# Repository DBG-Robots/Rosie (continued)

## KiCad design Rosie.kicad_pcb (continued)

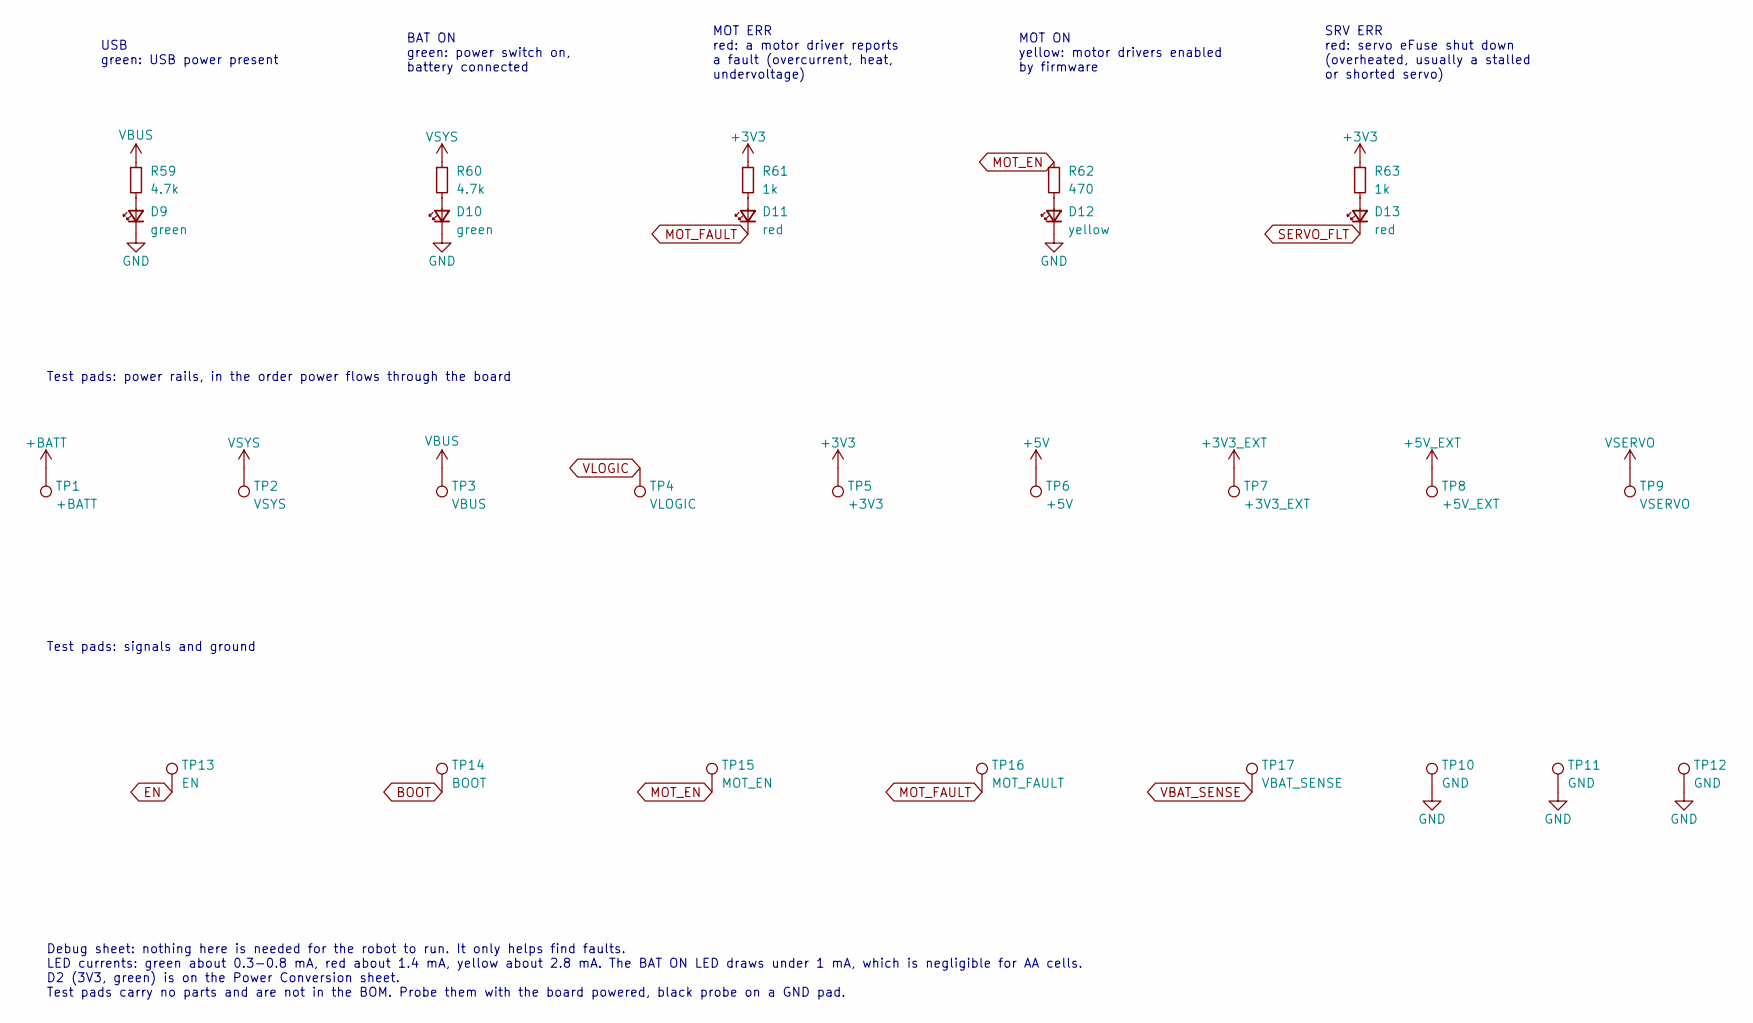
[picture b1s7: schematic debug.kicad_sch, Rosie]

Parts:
D9, D10: green; LED_0805_2012Metric; LCSC Part C2297
D11, D13: red; LED_0603_1608Metric; LCSC Part C2286
D12: yellow; LED_0805_2012Metric; LCSC Part C2296
R59, R60: 4.7k; R_0402_1005Metric
R61, R63: 1k; R_0402_1005Metric
R62: 470; R_0402_1005Metric
TP1: +BATT; TestPoint_Pad_D1.5mm
TP2: VSYS; TestPoint_Pad_D1.5mm
TP3: VBUS; TestPoint_Pad_D1.5mm
TP4: VLOGIC; TestPoint_Pad_D1.5mm
TP5: +3V3; TestPoint_Pad_D1.5mm
TP6: +5V; TestPoint_Pad_D1.5mm
TP7: +3V3_EXT; TestPoint_Pad_D1.5mm
TP8: +5V_EXT; TestPoint_Pad_D1.5mm
TP9: VSERVO; TestPoint_Pad_D1.5mm
TP10, TP11, TP12: GND; TestPoint_Pad_D1.5mm
TP13: EN; TestPoint_Pad_D1.5mm
TP14: BOOT; TestPoint_Pad_D1.5mm
TP15: MOT_EN; TestPoint_Pad_D1.5mm
TP16: MOT_FAULT; TestPoint_Pad_D1.5mm
TP17: VBAT_SENSE; TestPoint_Pad_D1.5mm

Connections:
+3V3: R61.1, R63.1, TP5.1; also elsewhere on the board
+3V3_EXT: TP7.1; also elsewhere on the board
+5V: TP6.1; also elsewhere on the board
+5V_EXT: TP8.1; also elsewhere on the board
+BATT: TP1.1; also elsewhere on the board
BOOT: TP14.1; also elsewhere on the board
EN: TP13.1; also elsewhere on the board
GND: D9.1 (K), D10.1 (K), D12.1 (K), TP10.1, TP11.1, TP12.1; also elsewhere on the board
MOT_EN: R62.1, TP15.1; also elsewhere on the board
MOT_FAULT: D11.1 (K), TP16.1; also elsewhere on the board
unnamed: D9.2 (A), R59.2
unnamed: D10.2 (A), R60.2
unnamed: D11.2 (A), R61.2
unnamed: D12.2 (A), R62.2
unnamed: D13.2 (A), R63.2
SERVO_FLT: D13.1 (K); also elsewhere on the board
VBAT_SENSE: TP17.1; also elsewhere on the board
VBUS: R59.1, TP3.1; also elsewhere on the board
VLOGIC: TP4.1; also elsewhere on the board
VSERVO: TP9.1; also elsewhere on the board
VSYS: R60.1, TP2.1; also elsewhere on the board

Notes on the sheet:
USB green: USB power present
BAT ON green: power switch on, battery connected
MOT ERR red: a motor driver reports a fault (overcurrent, heat, undervoltage)
MOT ON yellow: motor drivers enabled by firmware
SRV ERR red: servo eFuse shut down (overheated, usually a stalled or shorted servo)
Test pads: power rails, in the order power flows through the board
Test pads: signals and ground
Debug sheet: nothing here is needed for the robot to run. It only helps find faults. LED currents: green about 0.3-0.8 mA, red about 1.4 mA, yellow about 2.8 mA. The BAT ON LED draws under 1 mA, which is negligible for AA cells. D2 (3V3, green) is on the Power Conversion sheet. Test pads carry no p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

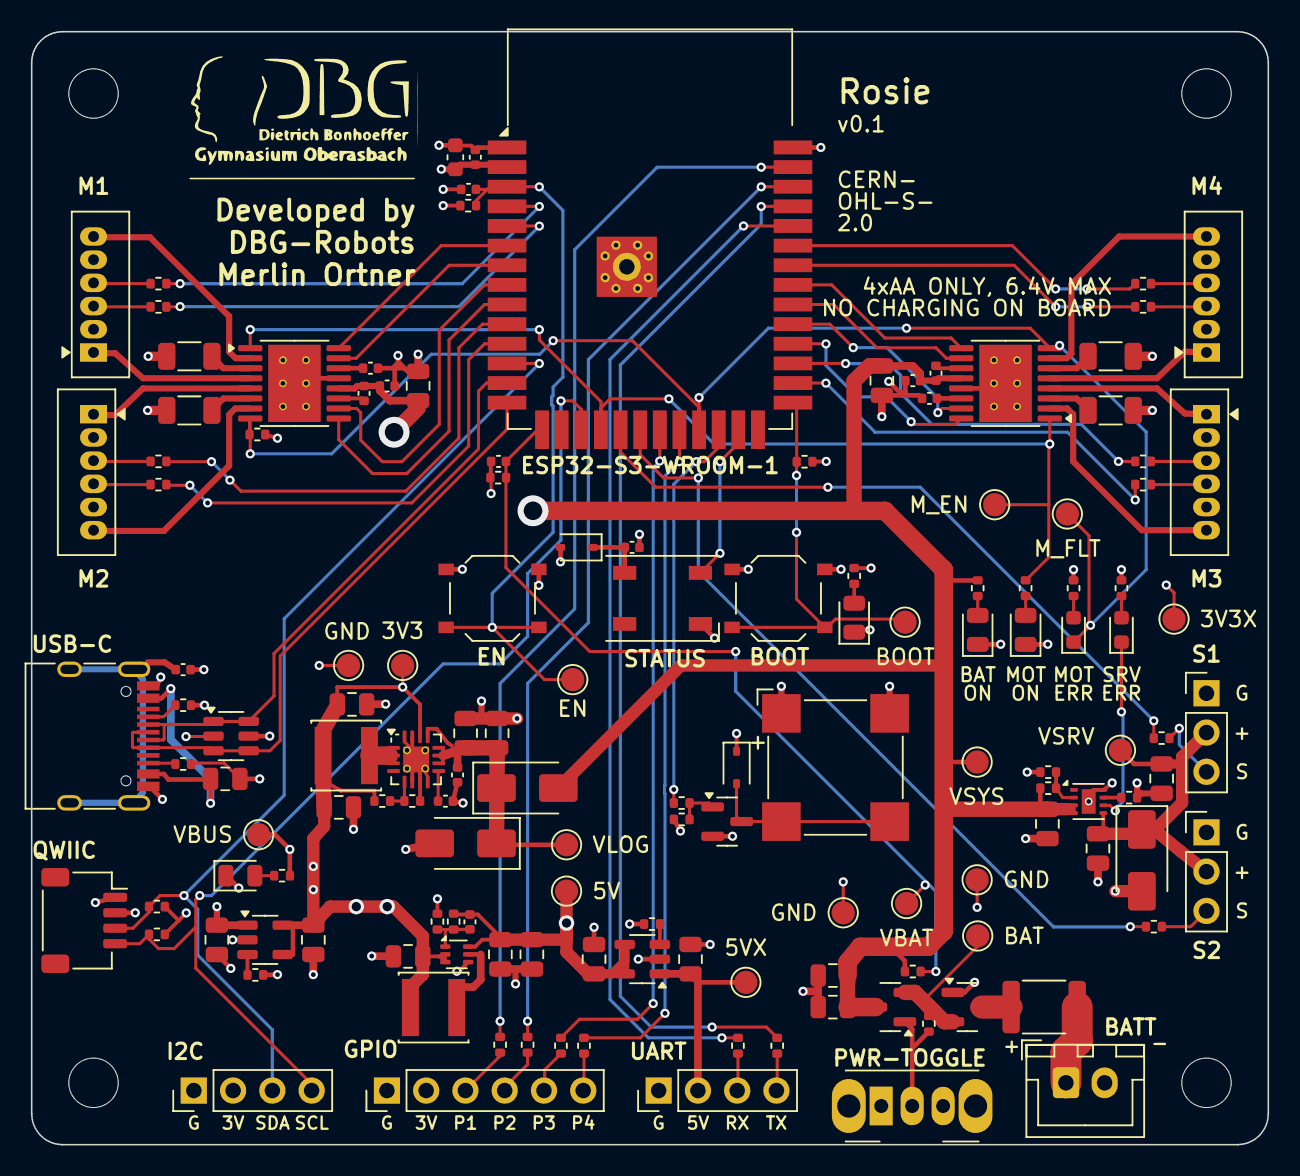
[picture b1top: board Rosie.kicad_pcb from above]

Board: 4 copper layers, 80.0 x 72.0 mm, 145 parts (0 on the bottom side), 102 nets.

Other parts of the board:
H1, H2, H3, H4: MountingHole_3.2mm_M3

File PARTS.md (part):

# Rosie – picked parts

JLCPCB **Economic PCBA only**. Basic/Preferred parts are free; each unique Extended part costs $3.07 per order.
Every pick below was checked as Economic-eligible and in stock on 2026-11-03 (power parts for the 4×AA design: 2026-11-04).

**Battery:** 4×AA in a flat holder under the board (NiMH 1900–2500 mAh, about 3 h; alkaline works too), 4.0–6.4 V.
The board never charges the cells: charge them in an external AA charger.
Resistors and capacitors aren't listed: JLC matches them by value and package. R43–R58 are 1 kΩ series resistors protecting every encoder, servo, UART and GPIO signal, so the pins on J12 can only source or sink about 1–2 mA. R59–R63 are the debug LED resistors (see below). Pick C47 (10 µF on VBUS) rated at least 16 V, because plugging in a USB cable can briefly overshoot 5 V.

## Assembled by JLC

| Function | Part | LCSC | Symbol | Footprint |
|---|---|---|---|---|
| Motor driver ×2 | DRV8833PWPR | C50506 | `Driver_Motor:DRV8833PWP` | `Package_SO:HTSSOP-16-1EP_4.4x5mm_P0.65mm_EP3.4x5mm_Mask2.46x2.31mm_ThermalVias` |
| 3.3 V buck (3–17 V in, 3 A, 100 % duty) | TPS62130ARGTR | C337502 | `Regulator_Switching:TPS62130A` | `Package_DFN_QFN:VQFN-16-1EP_3x3mm_P0.5mm_EP1.68x1.68mm_ThermalVias` |
| Servo eFuse (2 A, no OV clamp, auto-retry) | TPS259571DSGR | C471038 | `jlc:TPS259571DSG` | `Package_SON:WSON-8-1EP_2x2mm_P0.5mm_EP0.9x1.6mm` |
| Schottky ×3 (D6, D7: logic supply OR, battery / USB; D8: servo output clamp) | SS34 | C8678 (Basic) | `Diode:SS34` | `Diode_SMD:D_SMA` |
| Resettable fuse (3 A hold / 5 A trip, 8 V) | ASMD1812-300 | C135366 | `Device:Polyfuse` | `Fuse:Fuse_1812_4532Metric` |
| 5 V boost (from 3.3 V) | TPS61023DRLR | C919459 | `jlc:TPS61023DRL` | `Package_TO_SOT_SMD:SOT-563` |
| Current-limited switch ×2 (ext. 5 V / ext. 3.3 V) | SY6280AAC | C55136 | `jlc:SY6280AAC` | `Package_TO_SOT_SMD:SOT-23-5` |
| 1 µH inductor ×2 (18 mΩ, 4.7 A / 5.7 A) | FNR4030S1R0MT | C167865 | `Device:L` | `Inductor_SMD:L_Changjiang_FNR4030S` |
| P-FET ×2 (battery reverse polarity, power switch) | AO3401A | C15127 (Basic) | `Transistor_FET:AO3401A` | `Package_TO_SOT_SMD:SOT-23` |
| Qwiic I2C socket (J7) | JST SM04B-SRSS-TB(LF)(SN) | C160404 | `Connector_Generic:Conn_01x04` | `Connector_JST:JST_SH_SM04B-SRSS-TB_1x04-1MP_P1.00mm_Horizontal` |
| USB ESD | USBLC6-2SC6 | C7519 | `Power_Protection:USBLC6-2SC6` | `Package_TO_SOT_SMD:SOT-23-6` |
| USB-C receptacle | HRO TYPE-C-31-M-12 | C165948 | `Connector:USB_C_Receptacle_USB2.0_16P` | `Connector_USB:USB_C_Receptacle_HRO_TYPE-C-31-M-12` |
| RGB LED (WS2812B-compatible, 1 VDD / 2 DO / 3 GND / 4 DI) | XL-5050RGBC-2812B-HM | C48586674 | `LED:WS2812B` | `LED_SMD:LED_WS2812B_PLCC4_5.0x5.0mm_P3.2mm` |
| Buzzer (magnetic, 16 Ω) | MLT-8530 | C94599 | `Device:Buzzer` | `jlc:Buzzer_Huaneng_MLT-8530` |
| Buzzer driver NPN | MMBT3904 | C20526 (Basic) | `Transistor_BJT:MMBT3904` | `Package_TO_SOT_SMD:SOT-23` |
| Diode (buzzer flyback, RGB LED supply drop) | 1N4148WS | C2128 (Basic) | `Diode:1N4148WS` | `Diode_SMD:D_SOD-323` |
| Power LEDs, green (D2 3V3, D9 USB, D10 BAT ON) | KT-0805G | C2297 (Basic) | `Device:LED_Small` | `LED_SMD:LED_0805_2012Metric` |
| Motors-enabled LED, yellow (D12 MOT ON) | KT-0805Y | C2296 (Basic) | `Device:LED_Small` | `LED_SMD:LED_0805_2012Metric` |
| Fault LEDs, red (D11 MOT ERR, D13 SRV ERR) | KT-0603R | C2286 (Basic) | `Device:LED_Small` | `LED_SMD:LED_0603_1608Metric` |
| EN / BOOT buttons | TS-1187A-B-A-B | C318884 (Basic) | `Switch:SW_Push` | `Button_Switch_SMD:SW_Push_1P1T_XKB_TS-1187A` |

## Hand-soldered (order from LCSC, not placed by JLC)

| Function | Part | LCSC | Symbol | Footprint |
|---|---|---|---|---|
| MCU module | ESP32-S3-WROOM-1-N8R2 | C2913204 | `RF_Module:ESP32-S3-WROOM-1` | `jlc:ESP32-S3-WROOM-1_HandSolder` (longer pads, no paste, solder hole in the ground pad) |
| Power slide switch (right-angle) | SK12D07VG4 | C393937 | `Switch:SW_SPDT` | `Button_Switch_THT:SW_Slide_SPDT_Angled_CK_OS102011MA1Q` |
| Battery connector (keyed, 3 A) | XH-2A (JST XH 2-pin) | C2908600 | `Connector_Generic:Conn_01x02` | `Connector_JST:JST_XH_B2B-XH-A_1x02_P2.50mm_Vertical` |
| Battery holder | flat 4×AA holder with leads + JST-XH 2-pin pigtail (pin 1 = +) | – (any shop) | – | – |
| Motor + encoder connector ×2–4 (JST ZH 1.5 mm; 1 M1, 2 GND, 3 C1, 4 C2, 5 VCC, 6 M2) | JST B6B-ZR(LF)(SN) | C157984 | `Connector_Generic:Conn_01x06` | `jlc:JST_ZH_B6B-ZR_1x06_P1.50mm_Vertical` |
| Pin headers: servos, UART, GPIO, I2C (J8) | 1×40 male 2.54 mm (cut to length) | C42431788 | `Connector_Generic:Conn_01x0x` | `Connector_PinHeader_2.54mm:…` |

## Debug LEDs and test pads (Debug sheet)

None of this is needed for the robot to run. Green means power, yellow means motors enabled, red means a fault.

| LED | Silk | Lights when | Wiring |
|---|---|---|---|
| D2, green | 3V3 | +3V3 rail is up | +3V3 → R26 1 k → GND |
| D9, green | USB | USB power is present | VBUS → R59 4.7 k → GND |
| D10, green | BAT ON | switch on and battery connected | VSYS → R60 4.7 k → GND |
| D12, yellow | MOT ON | firmware enables the motor drivers | MOT_EN → R62 470 Ω → GND |
| D11, red | MOT ERR | a DRV8833 reports overcurrent, overheating or undervoltage | +3V3 → R61 1 k → MOT_FAULT |
| D13, red | SRV ERR | the servo eFuse overheats and shuts down (it doesn't light for current limiting alone) | +3V3 → R63 1 k → SERVO_FLT (TPS259571 pin 6) |

Test pads are 1.5 mm bare pads on the top side, with no part fitted and not in the BOM or position file.

| Silk | Net | Silk | Net |
|---|---|---|---|
| BAT | +BATT | 5VX | +5V_EXT |
| VSYS | VSYS | VSRV | VSERVO |
| VBUS | VBUS | GND (3 pads) | GND |
| VLOG | VLOGIC | EN | EN |
| 3V3 | +3V3 | BOOT | BOOT |
| 5V | +5V | M_EN / M_FLT | MOT_EN / MOT_FAULT |
| 3V3X | +3V3_EXT | VBAT | VBAT_SENSE |

## Motors (not on the board)

The motor connectors match the CHIHAI CHF-GM12-N20 hall-encoder motor, 6 V, with its 6-pin ZH 1.5 mm cable. Other N20 motors use other pin orders, and a wrong order can swap encoder VCC and GND.
Before first power, plug the motor into the unpowered board and check with a multimeter that the GND pad on the encoder connects to board GND.

## PCB

4 layers, 80×72 mm: top = parts and power routing, In1 = solid GND, In2 = +3V3 plane with thin +3V3_EXT, +5V and VBUS traces, bottom = free for signals.

## Project library (`libs/`)

- `jlc.kicad_sym`: TPS259571DSG, TPS61023DRL, SY6280AAC (drawn from the datasheets; KiCad's stock library doesn't have them), plus power symbols VSYS, VSERVO, +3V3_EXT, +5V_EXT
- `jlc.pretty`: ESP32-S3-WROOM-1_HandSolder, Buzzer_Huaneng_MLT-8530, JST_ZH_B6B-ZR_1x06_P1.50mm_Vertical (drawn from the JST datasheet; KiCad's stock library has no ZH), SOT-563_TI_DRL (TI's land pattern), and copies of the stock HTSSOP-16 and VQFN-16 footprints with 0.3 mm thermal vias (`_D0.3`)
- `jlc.3dshapes`: ESP32-S3-WROOM-1.step, plus simplified models of the buzzer, ZH connector, USB-C receptacle, tact switch and fuse. They are drawn from the datasheet outlines by `libs/3d-generator/make_models.py` (run with FreeCAD), so sizes, heights and pin positions are right but small details are missing.
- The stock KiCad footprints for the USB-C connector, the tact switches and the fuse point to model files that this KiCad install doesn't have, so the board uses the generated models for them. The two DRV8833s and the TPS62130 use the stock STEP models of the same packages.

## Resistors and capacitors (JLC part numbers)

Looked up on 2026-11-05: all in stock and Economic-eligible. **Basic** parts cost nothing extra; **Extended** parts cost $3.07 per unique part per order.

| Value | Package | Parts | LCSC | Type |
|---|---|---|---|---|
| 100 nF | 0402 | C2 C16 C23 C36 C40 C44 | C1525 (16 V) | Basic |
| 10 nF | 0402 | C28 C38 C42 | C15195 (50 V) | Basic |
| 1 µF | 0402 | C3 | C52923 (25 V) | Basic |
| 2.2 µF | 0402 | C37 C41 | C12530 (6.3 V, fine for the DRV8833 VINT pin) | Basic |
| 4.7 nF | 0402 | C24 C48 | C1538 (50 V) | Basic |
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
